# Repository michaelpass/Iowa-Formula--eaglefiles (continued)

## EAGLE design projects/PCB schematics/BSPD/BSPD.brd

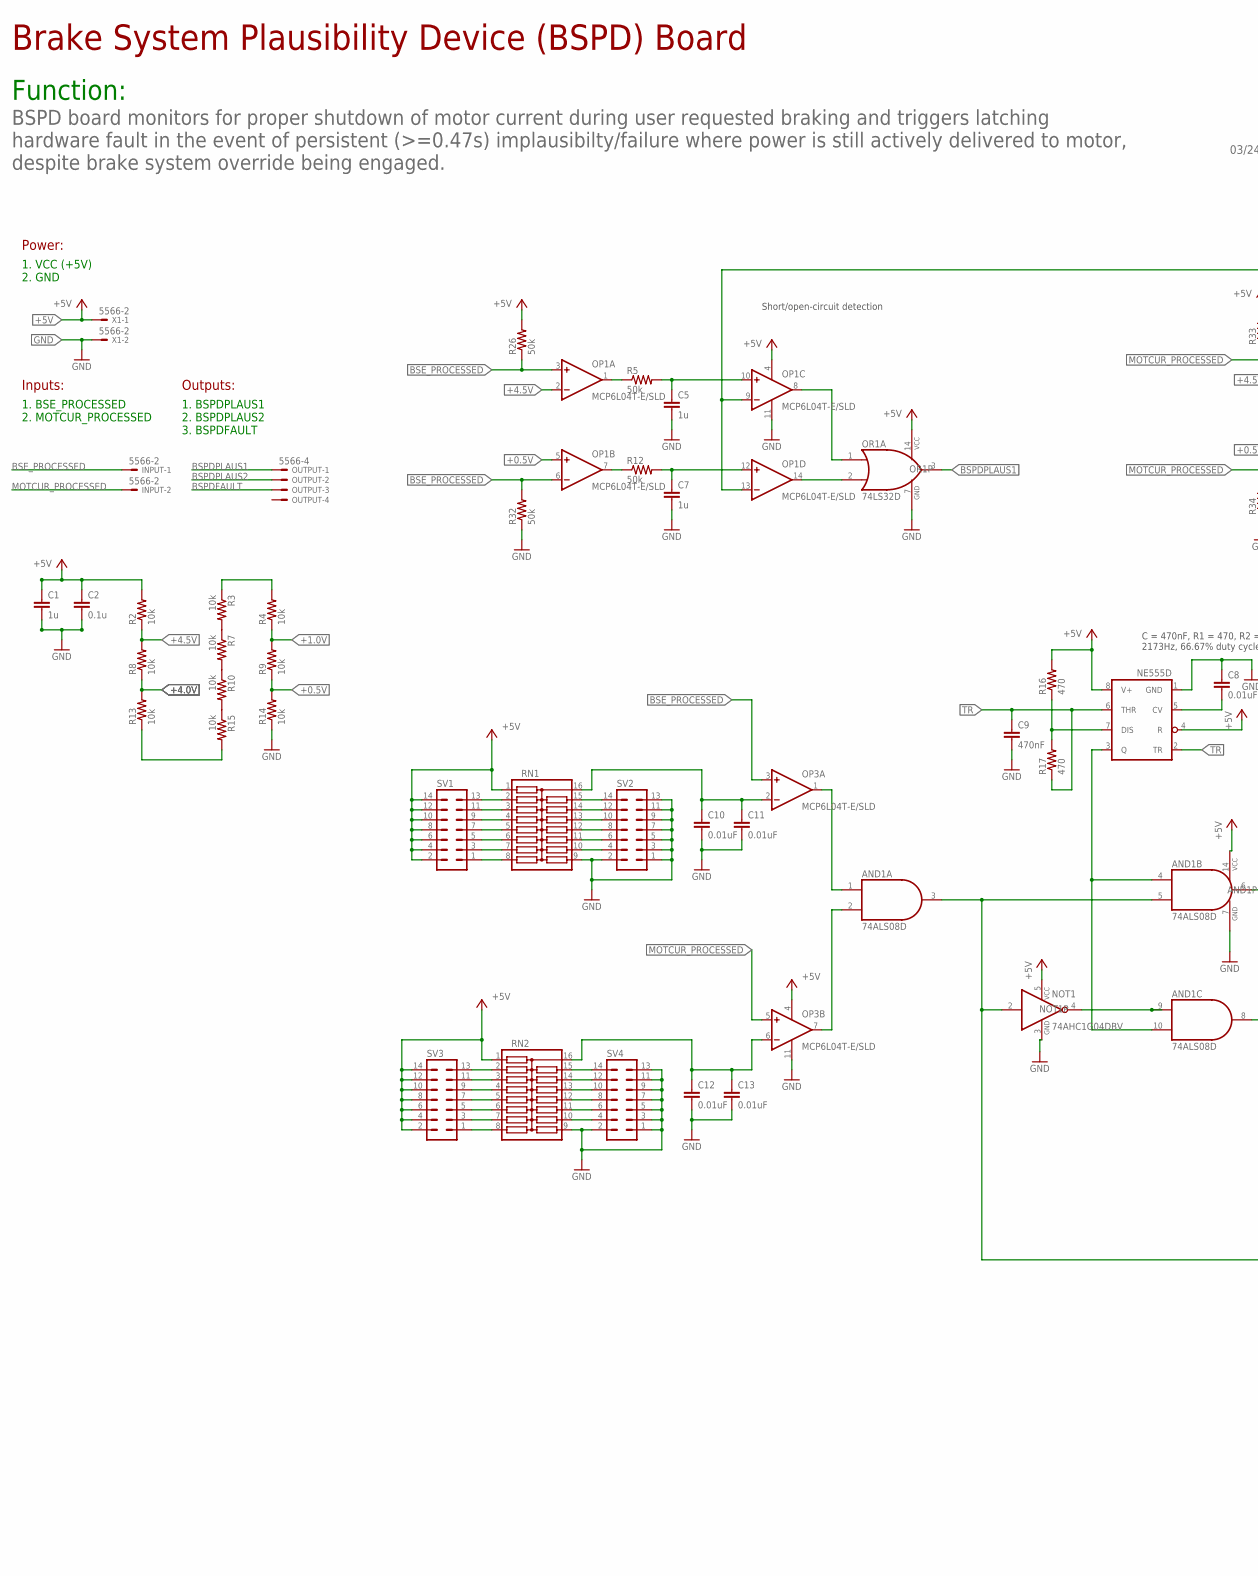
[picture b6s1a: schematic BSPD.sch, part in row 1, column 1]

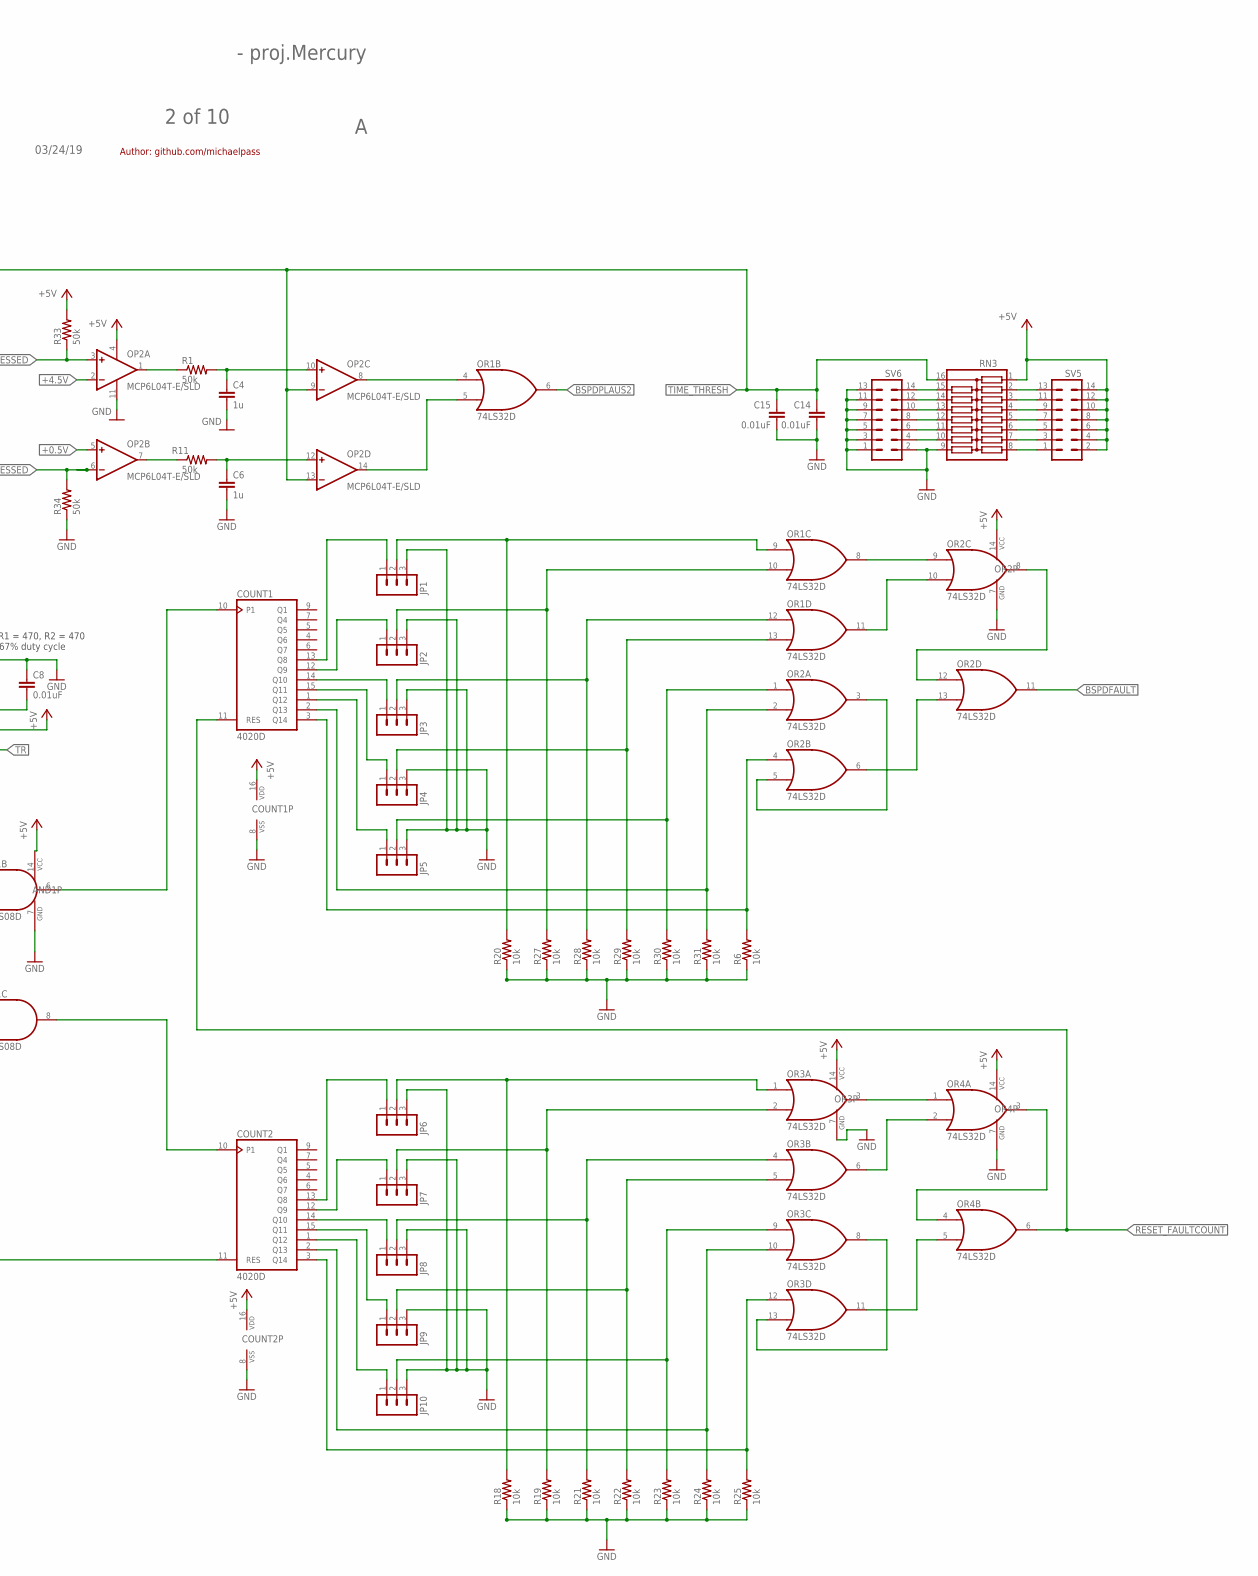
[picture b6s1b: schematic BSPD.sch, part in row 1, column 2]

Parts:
AND1: 74ALS08D; SO14
C1, C4, C5, C6, C7: 1u; C0805
C2: 0.1u; C0805
C8, C10, C11, C12, C13, C14, C15: 0.01uF; C0805
C9: 470nF; C0805
COUNT1, COUNT2: 4020D; SO16
INPUT: 5566-2
JP1, JP2, JP3, JP4, JP5, JP6, JP7, JP8, JP9, JP10: MA03-1
NE555D: NE555D; SO08
NOT1: 74AHC1G04DBV; SOT23-5
OP1, OP2, OP3: MCP6L04T-E/SLD; SO14
OR1, OR2, OR3, OR4: 74LS32D; SO14
OUTPUT: 5566-4
R1, R5, R11, R12, R26, R32, R33, R34: 50k; R0805
R2, R3, R4, R6, R7, R8, R9, R10, R13, R14, R15, R18, R19, R20, R21, R22, R23, R24, R25, R27, R28, R29, R30, R31: 10k; R0805
R16, R17: 470; R0805
RN1, RN2, RN3: 15RSOMC; SOMC16
SV1, SV2, SV3, SV4, SV5, SV6: MA07-2
X1: 5566-2

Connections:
+0.5V: OP1.5 (+IN), OP2.5 (+IN), R9.1, R14.2
+1.0V: R4.1, R9.2
+4.0V: R8.1, R13.2
+4.5V: OP1.2 (-IN), OP2.2 (-IN), R2.1, R8.2
+5V: AND1.14 (VCC), C1.1, C2.1, COUNT1.16 (VDD), COUNT2.16 (VDD), NE555D.4 (R), NE555D.8 (V+), NOT1.5 (VCC), OP1.4 (V+), OP2.4 (V+), OP3.4 (V+), OR1.14 (VCC), OR2.14 (VCC), OR3.14 (VCC), OR4.14 (VCC), R2.2, R16.2, R26.2, R33.2, RN1.1, RN2.1, RN3.1, SV1.2, SV1.4, SV1.6, SV1.8, SV1.10, SV1.12, SV1.14, SV3.2, SV3.4, SV3.6, SV3.8, SV3.10, SV3.12, SV3.14, SV5.2, SV5.4, SV5.6, SV5.8, SV5.10, SV5.12, SV5.14, X1.1
BSE_PROCESSED: INPUT.1, OP1.3 (+IN), OP1.6 (-IN), OP3.3 (+IN), R26.1, R32.2
BSPDFAULT: OR2.11 (O), OUTPUT.3
BSPDPLAUS1: OR1.3 (O), OUTPUT.1
BSPDPLAUS2: OR1.6 (O), OUTPUT.2
GND: AND1.7 (GND), C1.2, C2.2, C4.2, C5.2, C6.2, C7.2, C8.1, C9.2, C10.2, C11.2, C12.2, C13.2, C14.2, C15.2, COUNT1.8 (VSS), COUNT2.8 (VSS), JP1.3, JP2.3, JP3.3, JP4.3, JP5.3, JP6.3, JP7.3, JP8.3, JP9.3, JP10.3, NE555D.1 (GND), NOT1.3 (GND), OP1.11 (V-), OP2.11 (V-), OP3.11 (V-), OR1.7 (GND), OR2.7 (GND), OR3.7 (GND), OR4.7 (GND), R6.1, R14.1, R18.1, R19.1, R20.1, R21.1, R22.1, R23.1, R24.1, R25.1, R27.1, R28.1, R29.1, R30.1, R31.1, R32.1, R34.1, RN1.9, RN2.9, RN3.9, SV2.1, SV2.2, SV2.3, SV2.5, SV2.7, SV2.9, SV2.11, SV2.13, SV4.1, SV4.2, SV4.3, SV4.5, SV4.7, SV4.9, SV4.11, SV4.13, SV6.1, SV6.2, SV6.3, SV6.5, SV6.7, SV6.9, SV6.11, SV6.13, X1.2
MOTCUR_PROCESSED: INPUT.2, OP2.3 (+IN), OP2.6 (-IN), OP3.5 (+IN), R33.1, R34.2
unnamed: R13.1, R15.2
unnamed: R10.2, R15.1
unnamed: COUNT1.3 (Q14), OR2.4 (I0), R6.2
unnamed: R3.2, R7.1
unnamed: R3.1, R4.2
unnamed: R7.2, R10.1
unnamed: OP1.1 (OUT), R5.1
unnamed: OP1.7 (OUT), R12.1
unnamed: C5.1, OP1.10 (+IN), R5.2
unnamed: C7.1, OP1.12 (+IN), R12.2
unnamed: OP2.1 (OUT), R1.1
unnamed: C4.1, OP2.10 (+IN), R1.2
unnamed: C6.1, OP2.12 (+IN), R11.2
unnamed: OP2.7 (OUT), R11.1
unnamed: OR2.3 (O), OR2.5 (I1)
unnamed: RN1.2, SV1.13
unnamed: AND1.3 (O), AND1.5 (I1), COUNT2.11 (RES), NOT1.2 (I)
unnamed: OR1.8 (O), OR2.9 (I0)
unnamed: C10.1, C11.1, OP3.2 (-IN), RN1.16
unnamed: JP1.2, OR1.9 (I0), R20.2
unnamed: C12.1, C13.1, OP3.6 (-IN), RN2.16
unnamed: AND1.4 (I0), AND1.10 (I1), NE555D.3 (Q)
unnamed: OR2.8 (O), OR2.12 (I0)
unnamed: C8.2, NE555D.5 (CV)
unnamed: AND1.2 (I1), OP3.7 (OUT)
unnamed: AND1.1 (I0), OP3.1 (OUT)
unnamed: AND1.9 (I0), NOT1.4 (O)
unnamed: JP6.2, OR3.1 (I0), R18.2
unnamed: COUNT2.13 (Q8), JP6.1
unnamed: JP7.2, OR3.2 (I1), R19.2
unnamed: JP8.2, OR3.4 (I0), R21.2
unnamed: COUNT2.14 (Q10), JP8.1
unnamed: JP9.2, OR3.5 (I1), R22.2
unnamed: JP10.2, OR3.9 (I0), R23.2
unnamed: COUNT2.2 (Q13), OR3.10 (I1), R24.2
unnamed: COUNT2.12 (Q9), JP7.1
unnamed: COUNT1.13 (Q8), JP1.1
unnamed: JP2.2, OR1.10 (I1), R27.2
unnamed: AND1.8 (O), COUNT2.10 (P1)
unnamed: AND1.6 (O), COUNT1.10 (P1)
unnamed: OP1.8 (OUT), OR1.1 (I0)
unnamed: OP1.14 (OUT), OR1.2 (I1)
unnamed: OP2.8 (OUT), OR1.4 (I0)
unnamed: OP2.14 (OUT), OR1.5 (I1)
unnamed: JP3.2, OR1.12 (I0), R28.2
unnamed: COUNT1.14 (Q10), JP3.1
unnamed: JP4.2, OR1.13 (I1), R29.2
unnamed: JP5.2, OR2.1 (I0), R30.2
unnamed: COUNT2.15 (Q11), JP9.1
unnamed: OR4.3 (O), OR4.4 (I0)
unnamed: COUNT2.3 (Q14), OR3.12 (I0), R25.2
unnamed: COUNT1.2 (Q13), OR2.2 (I1), R31.2
unnamed: OR1.11 (O), OR2.10 (I1)
unnamed: RN1.3, SV1.11
unnamed: RN1.4, SV1.9
unnamed: RN1.5, SV1.7
unnamed: RN1.6, SV1.5
unnamed: NE555D.7 (DIS), R16.1, R17.2
unnamed: RN1.7, SV1.3
unnamed: RN1.8, SV1.1
unnamed: RN1.15, SV2.14
unnamed: RN1.14, SV2.12
unnamed: RN1.13, SV2.10
unnamed: RN1.12, SV2.8
unnamed: RN1.11, SV2.6
unnamed: RN1.10, SV2.4
unnamed: COUNT1.15 (Q11), JP4.1
unnamed: RN2.2, SV3.13
unnamed: RN2.3, SV3.11
unnamed: RN2.4, SV3.9
unnamed: RN2.5, SV3.7
unnamed: RN2.6, SV3.5
unnamed: RN2.7, SV3.3
unnamed: RN2.8, SV3.1
unnamed: RN2.15, SV4.14
unnamed: RN2.14, SV4.12
unnamed: RN2.13, SV4.10
unnamed: RN2.12, SV4.8
unnamed: RN2.11, SV4.6
unnamed: RN2.10, SV4.4
unnamed: RN3.2, SV5.13
unnamed: RN3.3, SV5.11
unnamed: RN3.4, SV5.9
unnamed: RN3.5, SV5.7
unnamed: RN3.6, SV5.5
unnamed: RN3.7, SV5.3
unnamed: RN3.8, SV5.1
unnamed: RN3.15, SV6.14
unnamed: RN3.14, SV6.12
unnamed: RN3.13, SV6.10
unnamed: RN3.12, SV6.8
unnamed: RN3.11, SV6.6
unnamed: RN3.10, SV6.4
unnamed: COUNT1.12 (Q9), JP2.1
unnamed: OR2.6 (O), OR2.13 (I1)
unnamed: COUNT1.1 (Q12), JP5.1
unnamed: COUNT2.1 (Q12), JP10.1
unnamed: OR3.8 (O), OR3.13 (I1)
unnamed: OR3.3 (O), OR4.1 (I0)
unnamed: OR3.6 (O), OR4.2 (I1)
unnamed: OR3.11 (O), OR4.5 (I1)
RESET_FAULTCOUNT: COUNT1.11 (RES), OR4.6 (O)
TIME_THRESH: C14.1, C15.1, OP1.9 (-IN), OP1.13 (-IN), OP2.9 (-IN), OP2.13 (-IN), RN3.16
TR: C9.1, NE555D.2 (TR), NE555D.6 (THR), R17.1

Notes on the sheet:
Brake System Plausibility Device (BSPD) Board
Function:
03/24/19
2 of 10
- proj.Mercury
BSPD board monitors for proper shutdown of motor current during user requested braking and triggers latching hardware fault in the event of persistent (>=0.47s) implausibilty/failure where power is still actively delivered to motor, despite brake system override being engaged.
Author: github.com/michaelpass
Inputs:
1. BSE_PROCESSED 2. MOTCUR_PROCESSED
Outputs:
1. BSPDPLAUS1 2. BSPDPLAUS2 3. BSPDFAULT
Power:
1. VCC (+5V) 2. GND
C = 470nF, R1 = 470, R2 = 470 2173Hz, 66.67% duty cycle
Short/open-circuit detection

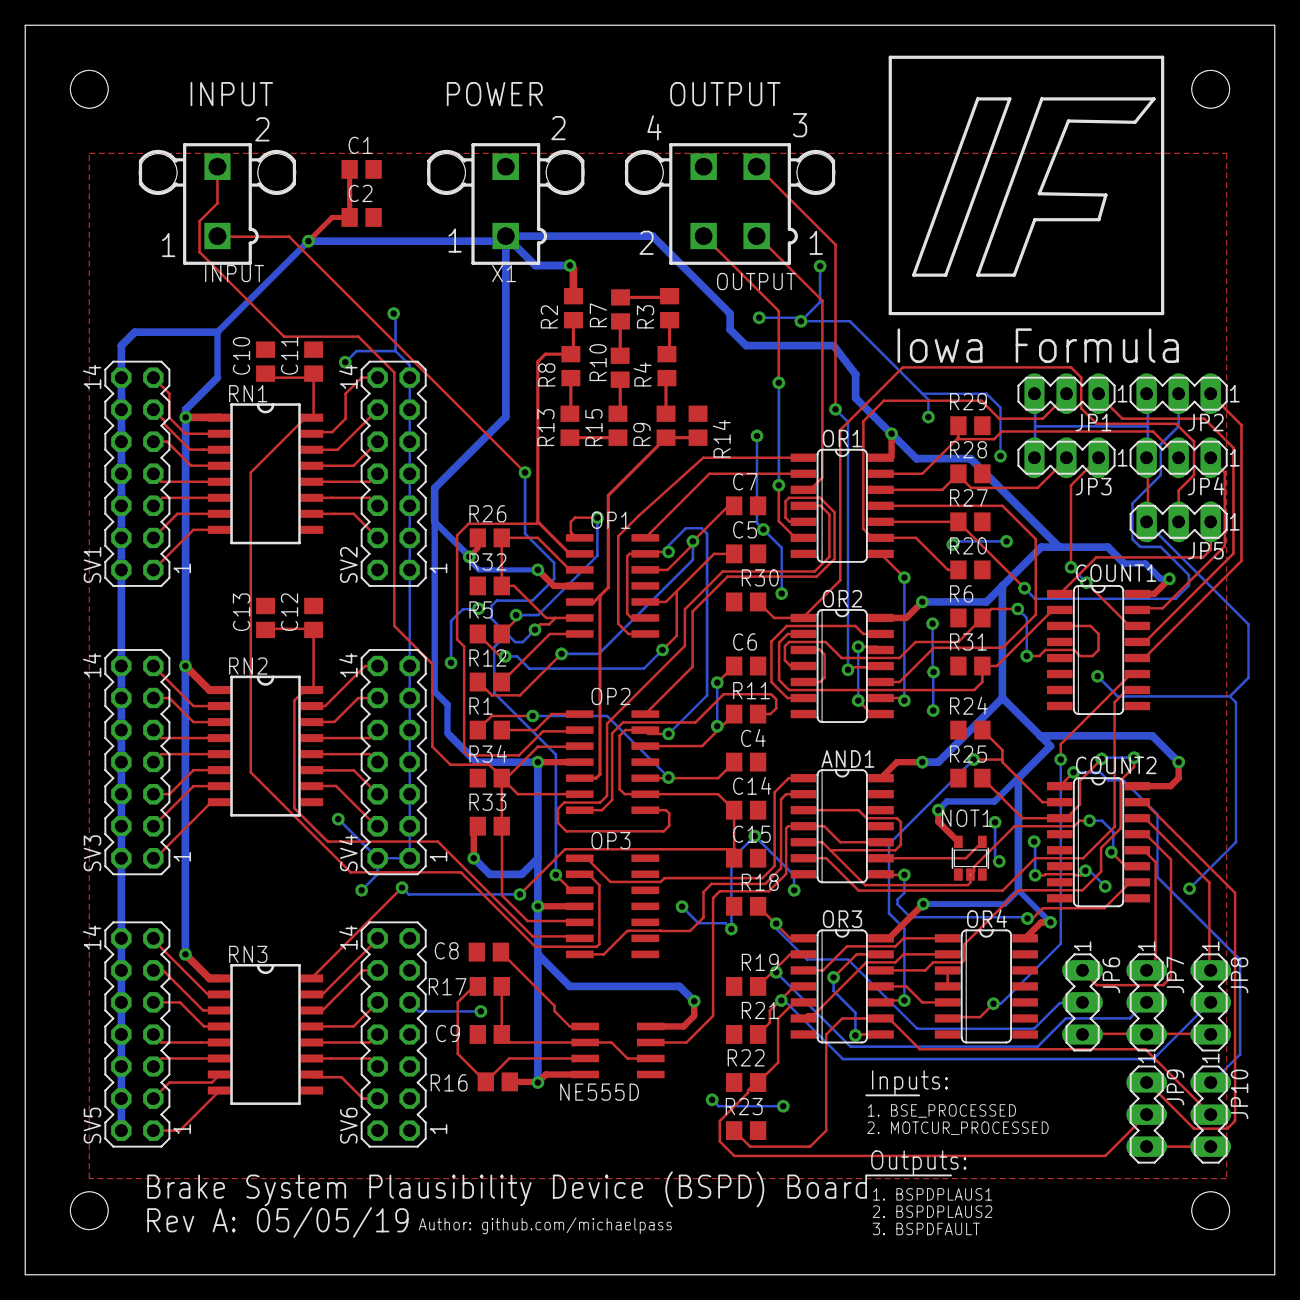
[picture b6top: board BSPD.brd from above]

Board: 2 copper layers, 99.1 x 99.1 mm, 82 parts (0 on the bottom side), 115 nets.

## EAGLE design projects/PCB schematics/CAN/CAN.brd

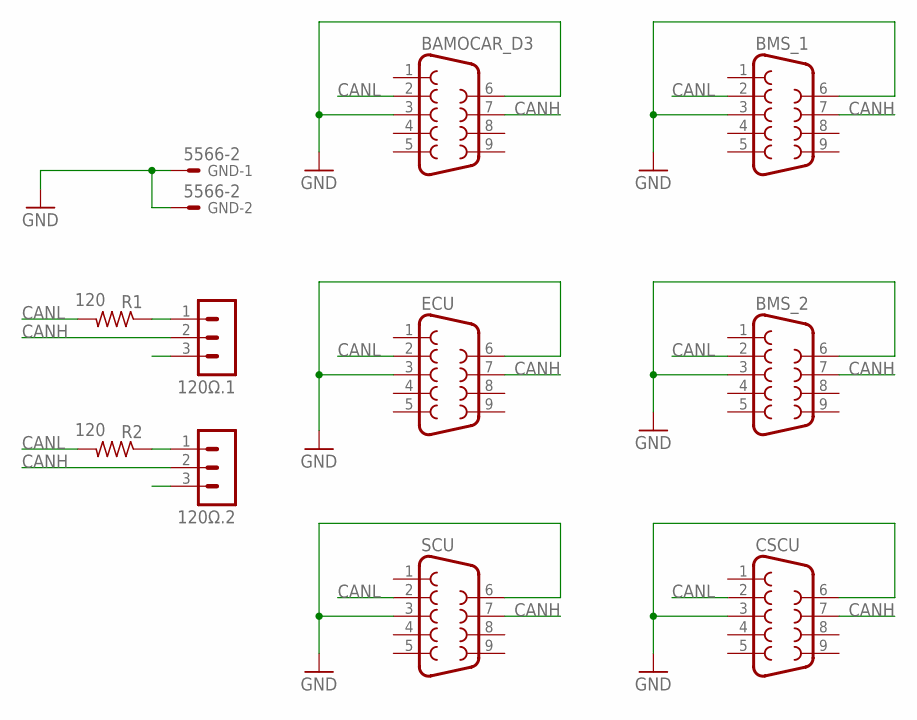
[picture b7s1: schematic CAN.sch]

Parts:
120Ω.1, 120Ω.2: MA03-1
BAMOCAR_D3: F09VP
BMS_1, BMS_2: F09VP
CSCU: F09VP
ECU: F09VP
GND: 5566-2
R1, R2: 120; R0805
SCU: F09VP

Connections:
CANH: 120Ω.1.2, 120Ω.2.2, BAMOCAR_D3.7, BMS_1.7, BMS_2.7, CSCU.7, ECU.7, SCU.7
CANL: BAMOCAR_D3.2, BMS_1.2, BMS_2.2, CSCU.2, ECU.2, R1.2, R2.2, SCU.2
GND: BAMOCAR_D3.3, BAMOCAR_D3.6, BMS_1.3, BMS_1.6, BMS_2.3, BMS_2.6, CSCU.3, CSCU.6, ECU.3, ECU.6, GND.1, GND.2, SCU.3, SCU.6
unnamed: 120Ω.2.1, R2.1
unnamed: 120Ω.1.1, R1.1

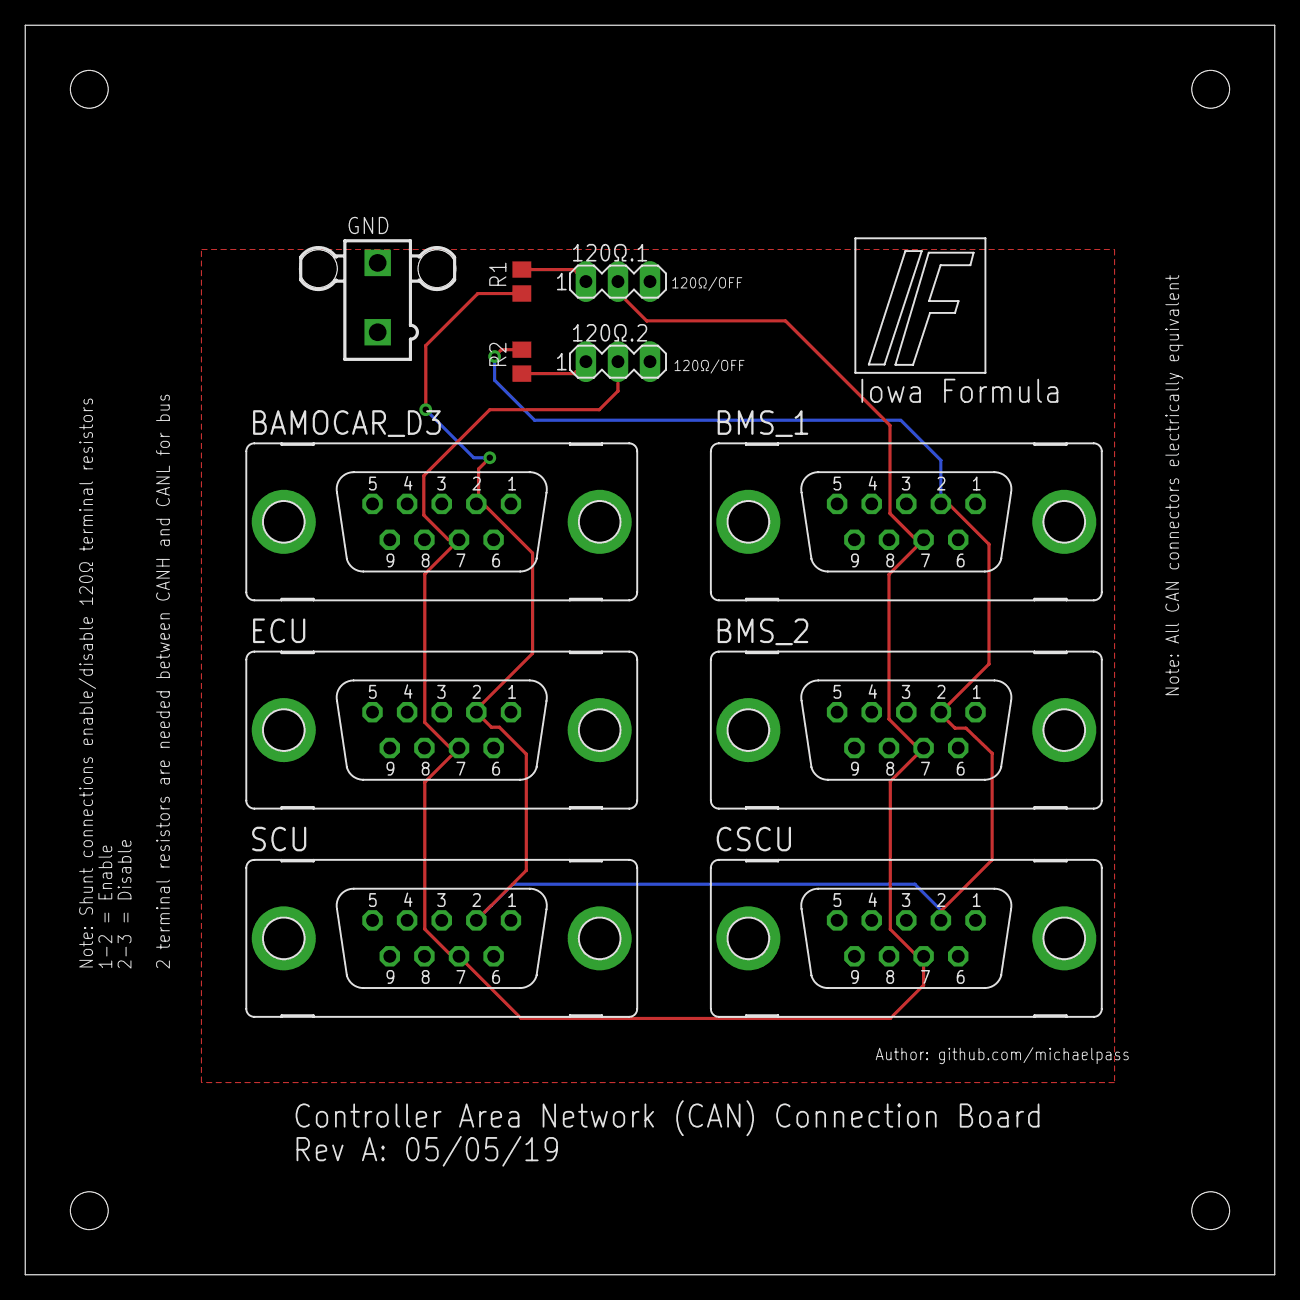
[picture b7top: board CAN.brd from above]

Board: 2 copper layers, 99.1 x 99.1 mm, 11 parts (0 on the bottom side), 5 nets.

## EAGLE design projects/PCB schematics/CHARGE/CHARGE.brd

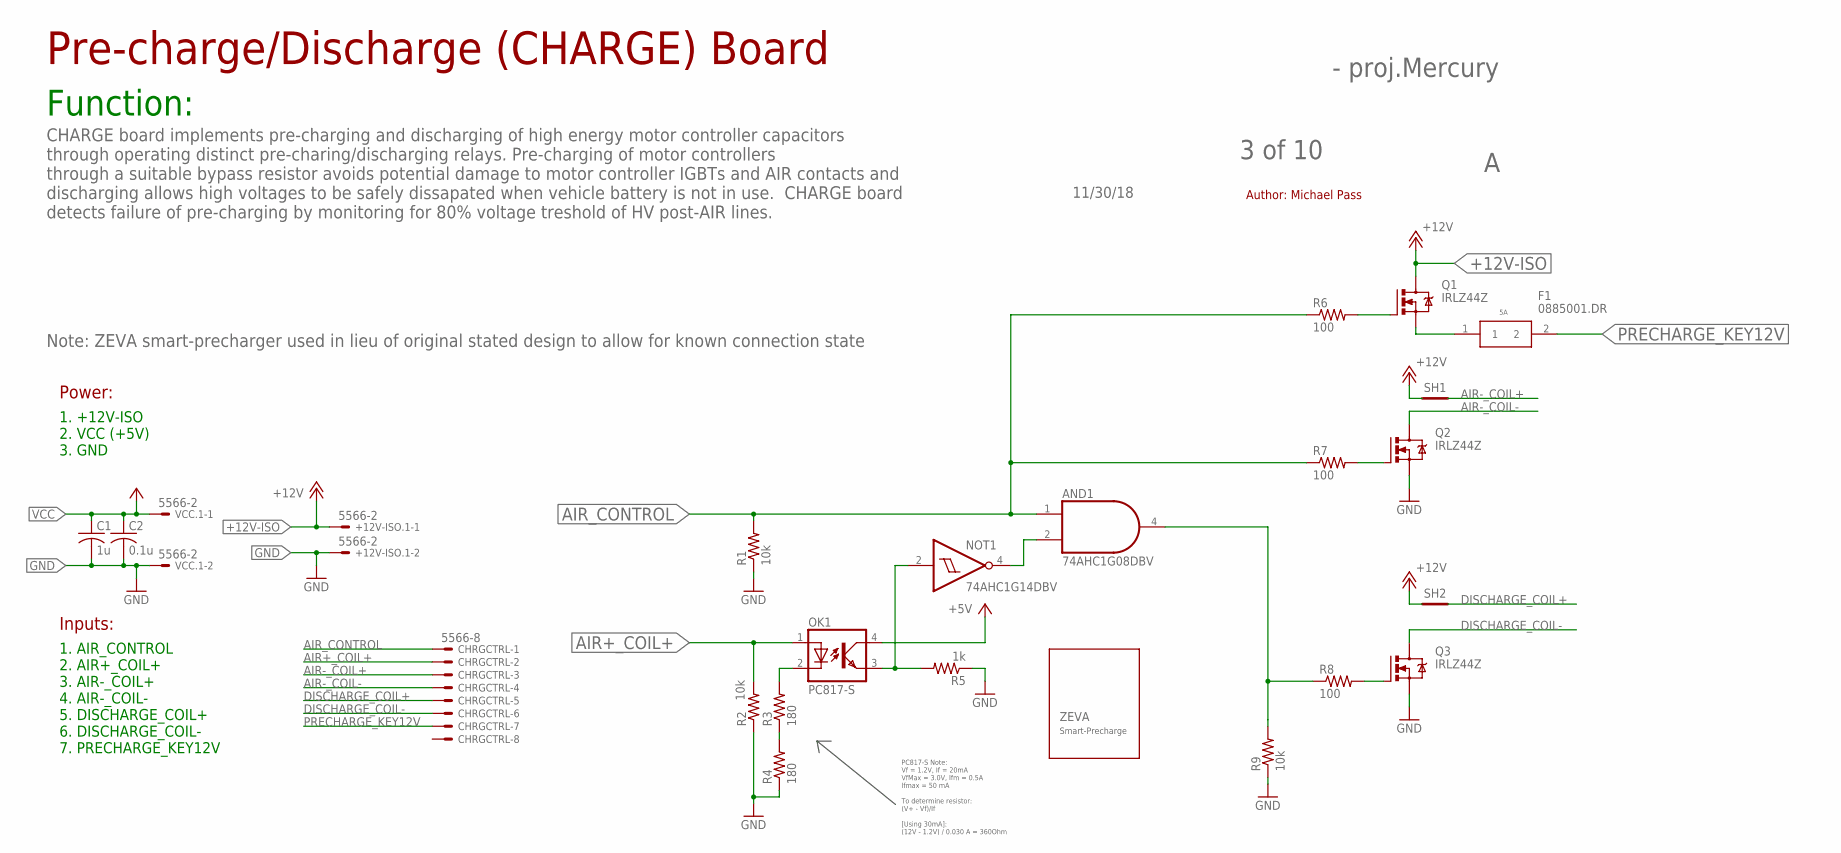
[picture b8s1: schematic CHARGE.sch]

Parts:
+12V-ISO.1: 5566-2
AND1: 74AHC1G08DBV; SOT23-5
C1: 1u; C0805
C2: 0.1u; C0805
CHRGCTRL: 5566-8
F1: 0885001.DR; FUSC10948X488N
NOT1: 74AHC1G14DBV; SOT23-5
OK1: PC817-S; SOP04(2.54)
Q1, Q2, Q3: IRLZ44Z; TO220BH
R1, R2, R9: 10k; R0805
R3, R4: 180; R0805
R5: 1k; R0805
R6, R7, R8: 100; R0805
SH1, SH2: SHORTA5; SHORT_ALL-50
U$1: ZEVA_SMART-PRECHARGE; ZEVA
VCC.1: 5566-2

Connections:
+12V-ISO: +12V-ISO.1.1, Q1.D, SH1.1, SH2.1
AIR+_COIL+: CHRGCTRL.2, OK1.1 (A), R2.2
AIR-_COIL+: CHRGCTRL.3, SH1.2
AIR-_COIL-: CHRGCTRL.4, Q2.D
AIR_CONTROL: AND1.1 (I0), CHRGCTRL.1, R1.2, R6.1, R7.1
DISCHARGE_COIL+: CHRGCTRL.5, SH2.2
DISCHARGE_COIL-: CHRGCTRL.6, Q3.D
DISCHARGE_MOSFET: AND1.4 (O), R8.1, R9.2
GND: +12V-ISO.1.2, AND1.3 (GND), C1.2, C2.2, NOT1.3 (GND), Q2.S, Q3.S, R1.1, R2.1, R4.1, R5.1, R9.1, VCC.1.2
unnamed: Q3.G, R8.2
unnamed: Q1.G, R6.2
unnamed: R3.1, R4.2
unnamed: Q2.G, R7.2
NO_PRECHRG: AND1.2 (I1), NOT1.4 (O)
OUTPUT77: NOT1.2 (I), OK1.3 (EMIT), R5.2
PRE-FUSE_PRECHARGE_KEY12V: F1.1, Q1.S
PRECHARGE_KEY12V: CHRGCTRL.7, F1.2
TAB11: OK1.2 (C), R3.2
VCC: AND1.5 (VCC), C1.1, C2.1, NOT1.5 (VCC), OK1.4 (COL), VCC.1.1

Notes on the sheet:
11/30/18
3 of 10
- proj.Mercury
Author: Michael Pass
Function:
CHARGE board implements pre-charging and discharging of high energy motor controller capacitors through operating distinct pre-charing/discharging relays. Pre-charging of motor controllers through a suitable bypass resistor avoids potential damage to motor controller IGBTs and AIR contacts and disc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
Pre-charge/Discharge (CHARGE) Board
Note: ZEVA smart-precharger used in lieu of original stated design to allow for known connection state
Inputs:
1. AIR_CONTROL 2. AIR+_COIL+ 3. AIR-_COIL+ 4. AIR-_COIL- 5. DISCHARGE_COIL+ 6. DISCHARGE_COIL- 7. PRECHARGE_KEY12V
Power:
1. +12V-ISO 2. VCC (+5V) 3. GND
PC817-S Note: Vf = 1.2V, If = 20mA VfMax = 3.0V, Ifm = 0.5A Ifmax = 50 mA To determine resistor: (V+ - Vf)/If [Using 30mA]: (12V - 1.2V) / 0.030 A = 360Ohm

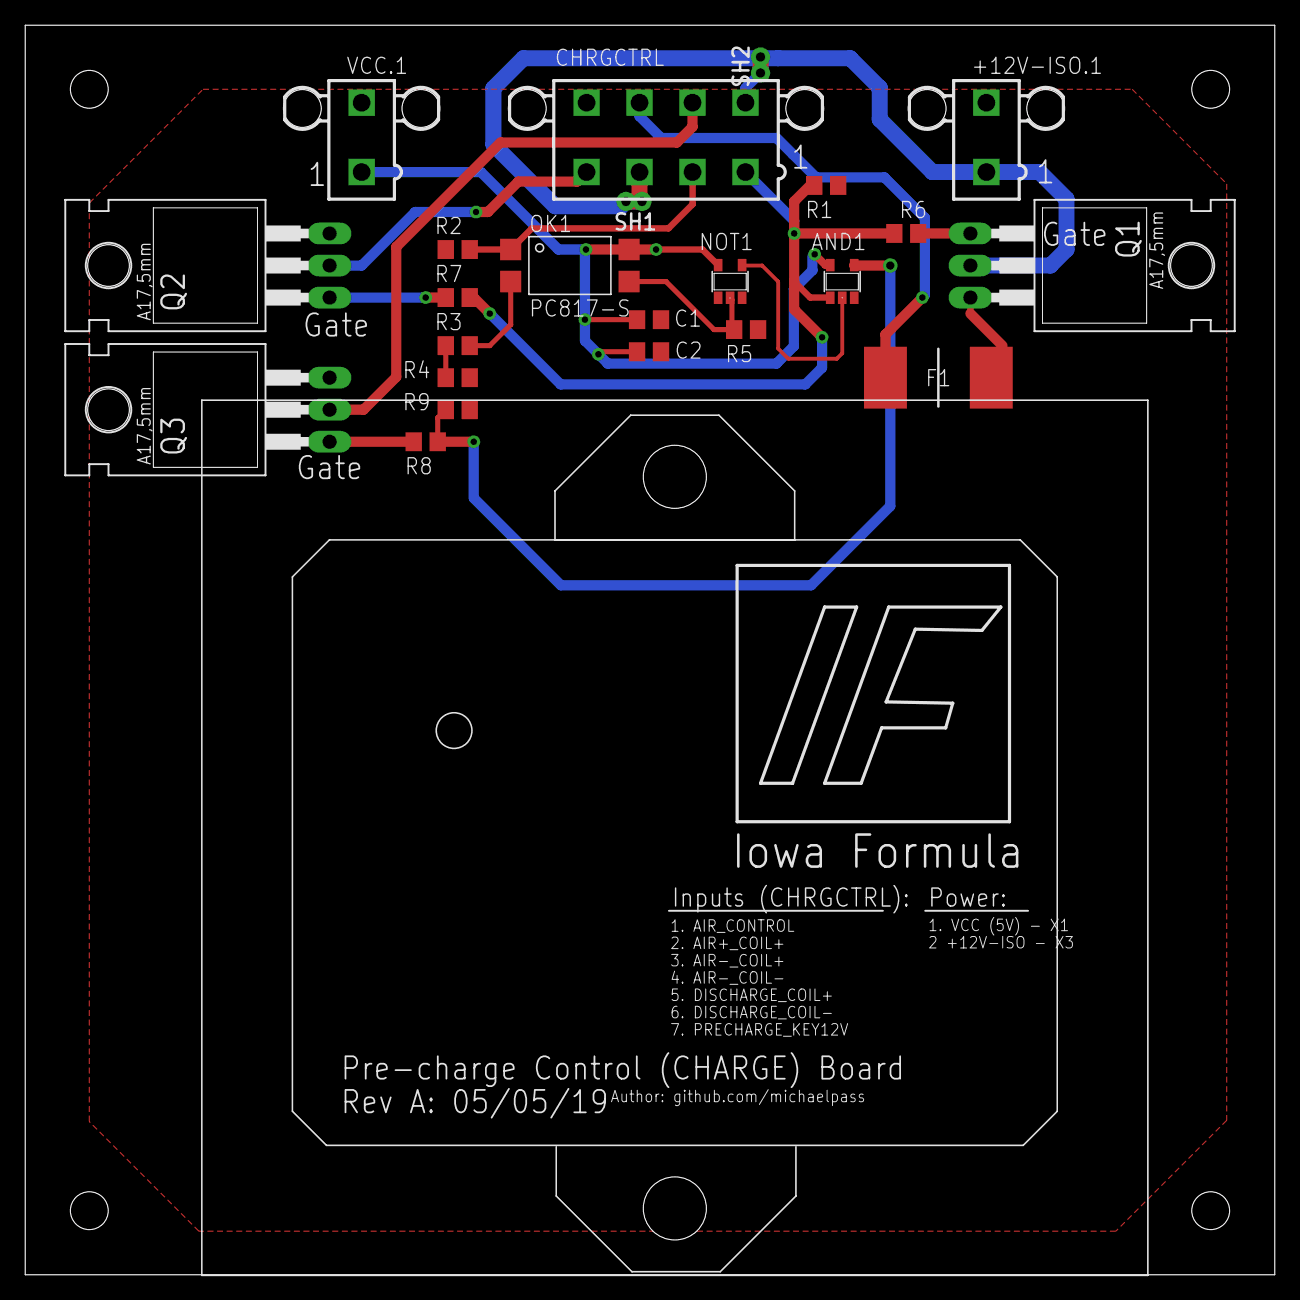
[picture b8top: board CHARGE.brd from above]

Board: 2 copper layers, 99.1 x 99.1 mm, 24 parts (0 on the bottom side), 19 nets.
